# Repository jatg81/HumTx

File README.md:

# HumTx
Mod Deshumedecedor de closet DHM150 IMACO

Se modifica el deshumedecedor para que vacie automaticamente el agua del recipiente interno y lo envie hacia un deposito externo, ademas se incorporo un sensor de humedad y temperatura del aire. Los datos del estado del humedecedor son enviados inalambricamente a un Raspberry Pi (EmonPi).

Caracteristicas de fabrica
- Modelo: DHM150
- Dimensiones: 21x17x13 cm
- Potencia: 25W
- Recipiente: 500mL
- Capacidad de remoción de humedad 200-300 ml/día

Principales componentes internos:
- *Microcontrolador: Moteino USB R6
- *Sensor de nivel: HC-SR04
- *Sensor humedad-temperatura: DHT22
- Enfriador celda peltier: TEC01-12703
- Ventilador: TX8025L12S
- *Bomba: Mini sumergible bomba de agua DC 2.5-6V -- 120L/H

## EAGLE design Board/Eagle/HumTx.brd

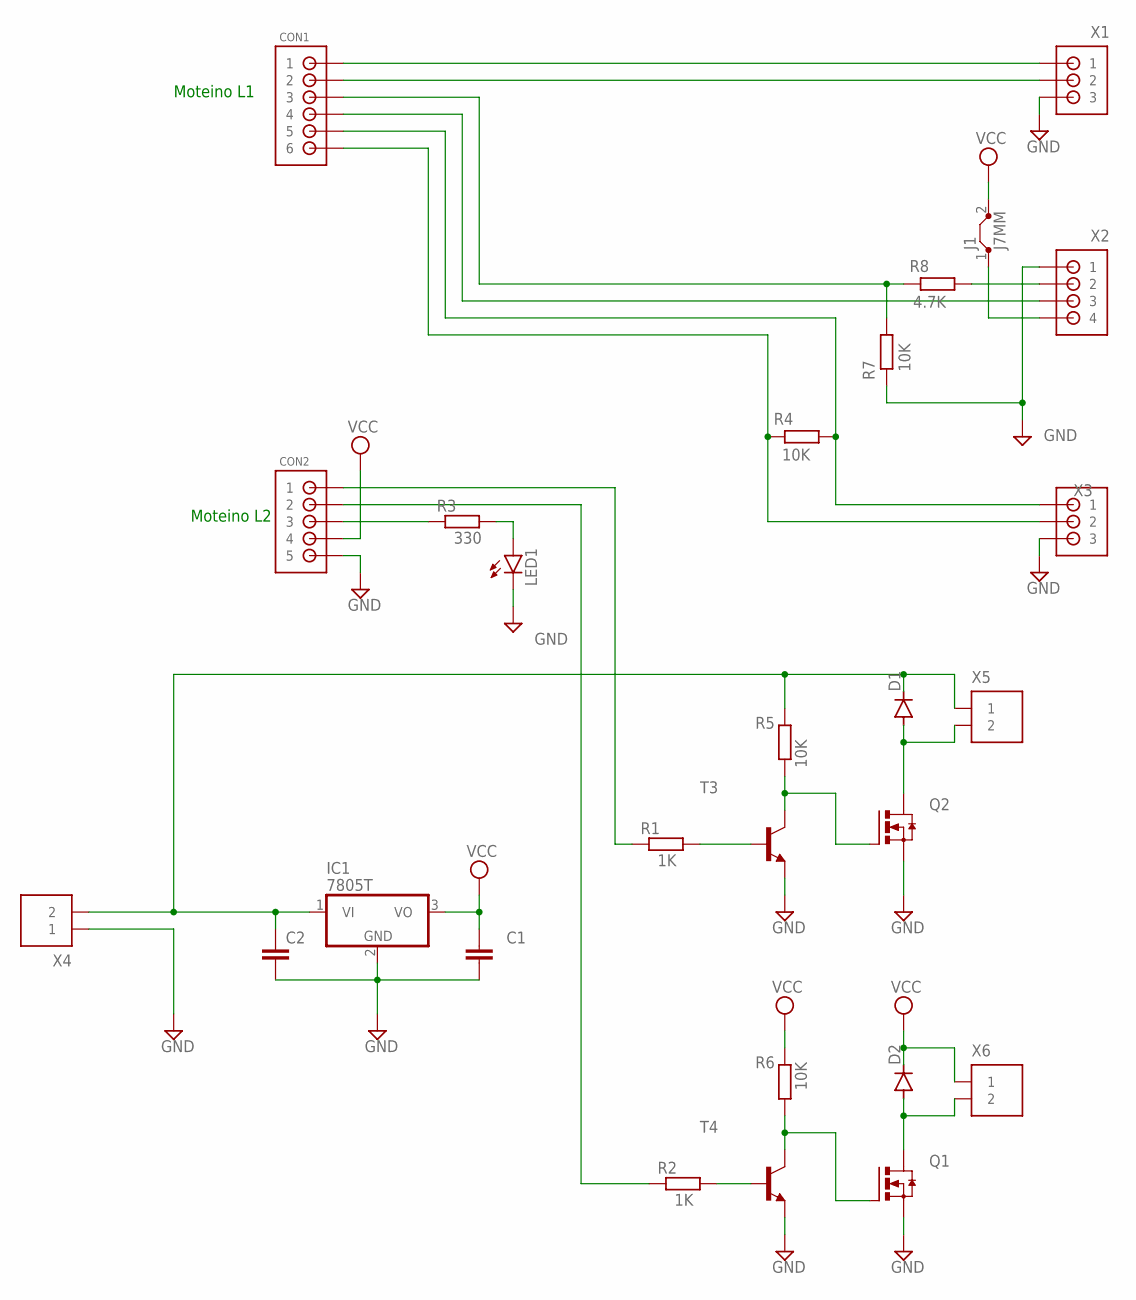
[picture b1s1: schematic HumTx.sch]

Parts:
C1, C2: C5/7.2; C5B7.2
CON1: B6B-ZR
CON2: B5B-ZR
D1, D2: 1N4004; DO41-10
IC1: 7805T; TO220H
J1: J7MM; 07
LED1: LED5MM
Q1, Q2: IRF3704-H; TO220BH
R1, R2: 1K; 0207/10
R3: 330; 0207/10
R4, R7: 10K; 0207/10
R5, R6: 10K; 0204/7
R8: 4.7K; 0207/10
T3, T4: -NPN-TO92-EBC; TO92-EBC
X1, X3: B3B-ZR
X2: B4B-ZR
X4, X5, X6: MKS1852-6-0-202

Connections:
GND: C1.2, C2.2, CON2.5, IC1.2 (GND), LED1.K (C), Q1.S, Q2.S, R7.2, T3.E, T4.E, X1.3, X2.1, X3.3, X4.1
unnamed: R2.2, T4.B
unnamed: R1.2, T3.B
unnamed: Q2.G, R5.1, T3.C
unnamed: LED1.A, R3.2
unnamed: D1.A, Q2.D, X5.2
unnamed: D2.A, Q1.D, X6.2
unnamed: CON1.5, R4.1, X3.1
unnamed: CON1.1, X1.1
unnamed: CON1.2, X1.2
unnamed: CON1.6, R4.2, X3.2
unnamed: CON1.4, X2.3
unnamed: CON1.3, R7.1, R8.2
unnamed: CON2.3, R3.1
unnamed: CON2.1, R1.1
unnamed: CON2.2, R2.1
unnamed: C2.1, D1.C, IC1.1 (VI), R5.2, X4.2, X5.1
unnamed: Q1.G, R6.1, T4.C
unnamed: R8.1, X2.2
unnamed: J1.1, X2.4
VCC: C1.1, CON2.4, D2.C, IC1.3 (VO), J1.2, R6.2, X6.1

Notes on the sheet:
Moteino L2
Moteino L1

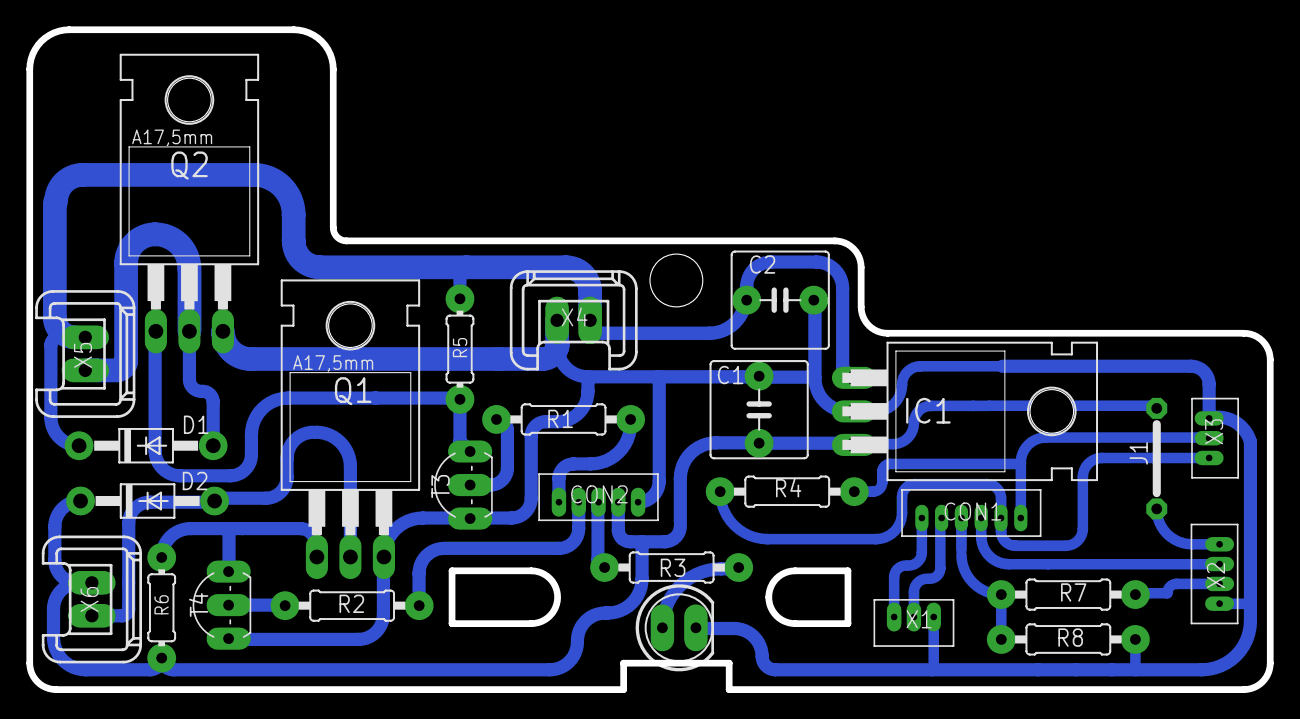
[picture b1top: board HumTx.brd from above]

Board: 2 copper layers, 94.0 x 50.0 mm, 27 parts (0 on the bottom side), 21 nets.

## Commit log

2018-12-12 v0.1
2018-12-17 test
2018-12-19 Create x
2018-12-19 Create d
2018-12-19 Rename Deshumecedor.brd to HumTx.brd
2018-12-19 Rename Deshumecedor.sch to HumTx.sch
2018-12-19 Create l
2018-12-19 Create g
2018-12-20 Create n
2018-12-20 Create f
